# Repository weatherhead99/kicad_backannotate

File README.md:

#  kicad_backannotator

A back annotation tool for [kicad](http://kicad-pcb.org)

Documentation and tutorial available [here](http://kicad-backannotate.readthedocs.io/en/latest/)

## Disclaimer

This is not in a finished state yet. ** DO NOT USE IT, ESPECIALLY NOT ON PRODUCTION BOARDS. I AM NOT RESPONSIBLE FOR BREAKING YOUR FILES **

## Installation
You require a working installation of PyQt5 and the kicad python bindings for kicad\_backannotate to run. Kicad\_backannotator only works on python 2 (this is a limitation of the kicad python bindings at the moment)

For now, you must install kicad_backannotate from a checked out source.

` git clone git@github.com:weatherhead99/kicad_backannotate.git `

You can install with
`python setup.py install`

or (preferred)

`pip install .`

You can build the documentation (such that it is) using

`python setup.py build_sphinx` 

and find the html documentation in the doc/build/html directory.

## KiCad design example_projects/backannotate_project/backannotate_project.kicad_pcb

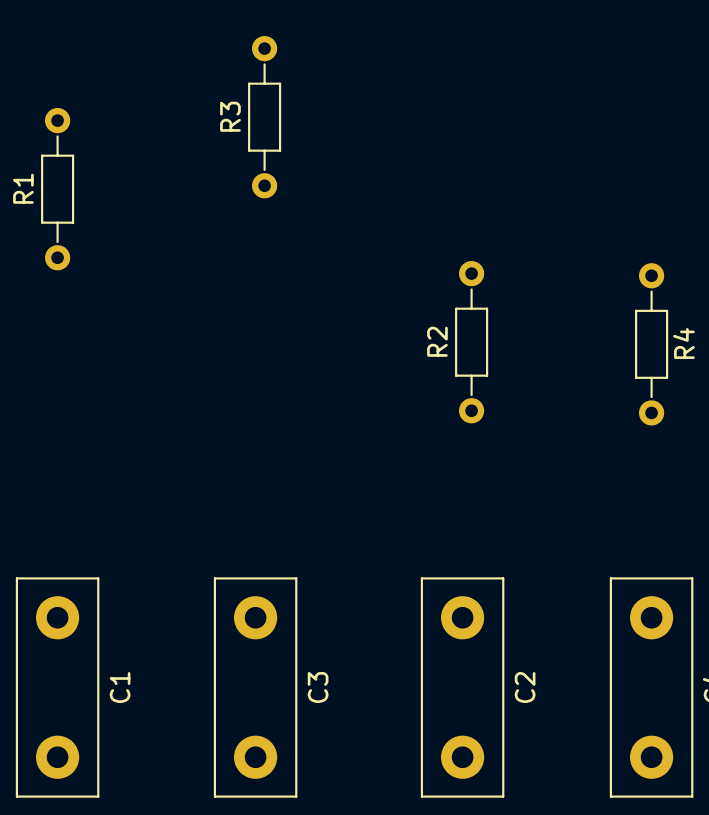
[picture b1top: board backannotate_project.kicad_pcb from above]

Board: 2 copper layers, 8 parts (0 on the bottom side), 6 nets, no tracks yet.

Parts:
C1, C2, C3, C4: C; C_Disc_D12.0mm_W4.4mm_P7.75mm
R1, R2, R3, R4: R; R_Axial_DIN0204_L3.6mm_D1.6mm_P7.62mm_Horizontal

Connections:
+15V: R1.1, R2.1, R3.1, R4.1
GND: C1.2, C2.2, C3.2, C4.2
unnamed: C1.1, R1.2
unnamed: C2.1, R2.2
unnamed: C3.1, R3.2
unnamed: C4.1, R4.2

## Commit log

2018-01-12 initial import
2018-01-12 basic logic and GUI skeleton
2018-01-12 distutils file
2018-01-12 package init files
2018-01-12 GUI main file
2018-01-12 updated GUI, board loading works...
2018-01-12 setup using pyqt_distutils
2018-01-13 added footprint properties display and units
2018-01-13 nearly working board commit changes
2018-01-13 licensing information
2018-01-13 update gui main
2018-01-13 skeleton readme
2018-01-13 update, still doesn't work properly
2018-01-13 add basic test for board remapper
2018-01-13 ok, board commit now kind of works
2018-01-13 rename main.py to something more sensible
2018-01-13 first sort of working schematic updater
2018-01-13 work on packaging
2018-01-13 add example project for tests
2018-01-13 remove extra path import
2018-01-13 use find_packages()
2018-01-13 test runnable from setup.py
2018-01-13 script to generate screenshots for doc
2018-01-13 more screenshots
2018-01-13 gui fix
2018-01-13 fix screenshot script
2018-01-13 add manual screenshots from kicad
2018-01-14 docs update
2018-01-14 documentation index and tutorial
2018-01-14 can now generate screenshots from setup.py
2018-01-14 forgot module file in doc
2018-01-14 add generated ui file
2018-01-14 add generated screenshots
2018-01-14 manifest file
2018-01-14 forgot init in test module
2018-01-14 fix setup for gui script
2018-01-14 use relative imports in gui
2018-01-14 more doc start page
2018-01-14 update docs
2018-01-14 update version number
2018-01-14 update readme with very basic doc
2018-01-14 add link to readthedocs
2018-01-14 add find_symbol to schematic updater, add some basic tests for SchematicUpdater
2018-01-14 add class for patching in compatibilty for older versions of pcbnew bindings at runtime
2018-01-14 change BoardRemapper to use compatibility metaclass
2018-01-14 fix compatibility layer error
2018-01-14 allow sorting in the symbol table
2018-01-14 improve model performance
2018-01-14 enable filtering in table view
2018-01-20 add python_requires, description and classifiers to setup script
2018-01-20 change version to 0.0.1
2018-01-20 fix compatibility for newer pcbnew.so where FPID() object doesn't exist
2018-01-26 add travis file
2018-01-26 update travis python test script
2018-01-26 try travis config again
2018-01-26 use miniconda since no pyqt5 for python2 on trusty
2018-01-26 error in conda config
2018-01-26 install kicad and pyqt on travis
2018-01-26 fix pyqt install
